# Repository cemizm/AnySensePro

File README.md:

# AnySense Pro
The AnySense Pro (aka 2.0) is an onboard flight logger and real-time telemetry system for (mainly) multicopters with versatile interfacing to various flight controllers, sensors and telemetry protocols. It is a further development of the [AnySense](https://github.com/cemizm/AnySense) and provides a more powerfull MCU (STM32F3) an SD-Card interface and USB connectivity for configuration and updates. A detailed description of the AnySense Pro can be found in the [manual](Dokumentation/AnySense_Pro_EN_.pdf) and in sources of the [main application](Firmware/shared/Application/source).

## Features
The aim of the AnySense Pro is to build a bridge between multiple proprietary systems and protocols in order to reduce the total take-off weight of the flight object. This is achived by reusing any existing sensor (source) of the integrated flight controller in a multicopter, and feeding the telemetry data to various sinks like the onboard SD-Card or real-time telemetrie return channel. 

### Flight Controller (source)
The AnySense Pro supports a wide range of open source and commercial flight controllers. A full list of provided sensors of each flight controller can be found in the [Manual](Dokumentation/AnySense_Pro_EN_.pdf). The flight controller connector provides 5V power supply, a CAN-Bus interface and full-duplex uart interface. 

| | |
|:---------:|:-----------:|
|  |  |

* [DJI Naza-M V1 / Lite](https://www.dji.com/de/naza-m-lite/feature)
* [DJI Naza-M V2](https://www.dji.com/de/naza-m-v2)
* [DJI Wookong](https://www.dji.com/de/wookong-m)
* [DJI A2](https://www.dji.com/de/a2)
* [DJI Phantom 2](https://www.dji.com/de/phantom-2)
* [3DR Pixhawk](https://docs.px4.io/master/en/flight_controller/mro_pixhawk.html)
* [Tarot ZYX-M](http://www.tarotrc.com/Product/Detail.aspx?Lang=en&Id=65341cc3-7941-4a12-84ea-8abc58bd59e7)
* [Align MRS](https://www.align.com.tw/index.php/download-en/mrs/)

Depending on the flight control, a corresponding cable with connectors and pin assignment is required. The pin assignment defines which hardware interface is used. The pinout of the flight controller connector on the AnySense Pro can be found in the [Schematics](Hardware/Pro/AnySensePro.pdf) or in some [example cables](Hardware/Kabel/CANBusKabel.pdf).

### FrSky Sensor (source)
Additionally to the integrated sensor of the flight controller, it is possible to use sensor of the vendor FrSky to obtain further telemetry data like a current sensor to measure total current consumption or a cell voltage sensor to monitor individual cells of the battery pack. The full list of supported sensors and implementation details can be found in the [source code](Firmware/shared/Application/source/SensorFrSky.cpp).

| | |
|:---------:|:-----------:|
|  |  |

The FrSky sensors run as a bus system and can therefore be daisy-chained together. for this purpose, each sensor offers two interconnected ports. The AnySense Pro acts as the master and each sensor operates as a slave. 

### USB
The USB interface of the AnySense Pro is used for configuration and firmware updates. The AnySense Pro implements an [USB-CDC device](Firmware/shared/Middleware/USB/source/USBCDCDevice.cpp) for serial communication with the host. The [host driver](Firmware/shared/driver/AnySensePro.inf) for the AnySense Pro uses [Microsoft provided in-box driver](https://docs.microsoft.com/en-us/windows-hardware/drivers/usbcon/usb-driver-installation-based-on-compatible-ids) with custom vendor and product ids. The AnySense Studio is a .NET WPF Application and can be used for configuration and firmware updates.
| | |
|:---------:|:-----------:|
|  |  |

### Micro SD (sink)

### Telemetry (sink)

### MAVLink OSD (sink)

## Project / Repository structure 

### Hardware
### Firmware
### GroundTools
### Dokumnetation

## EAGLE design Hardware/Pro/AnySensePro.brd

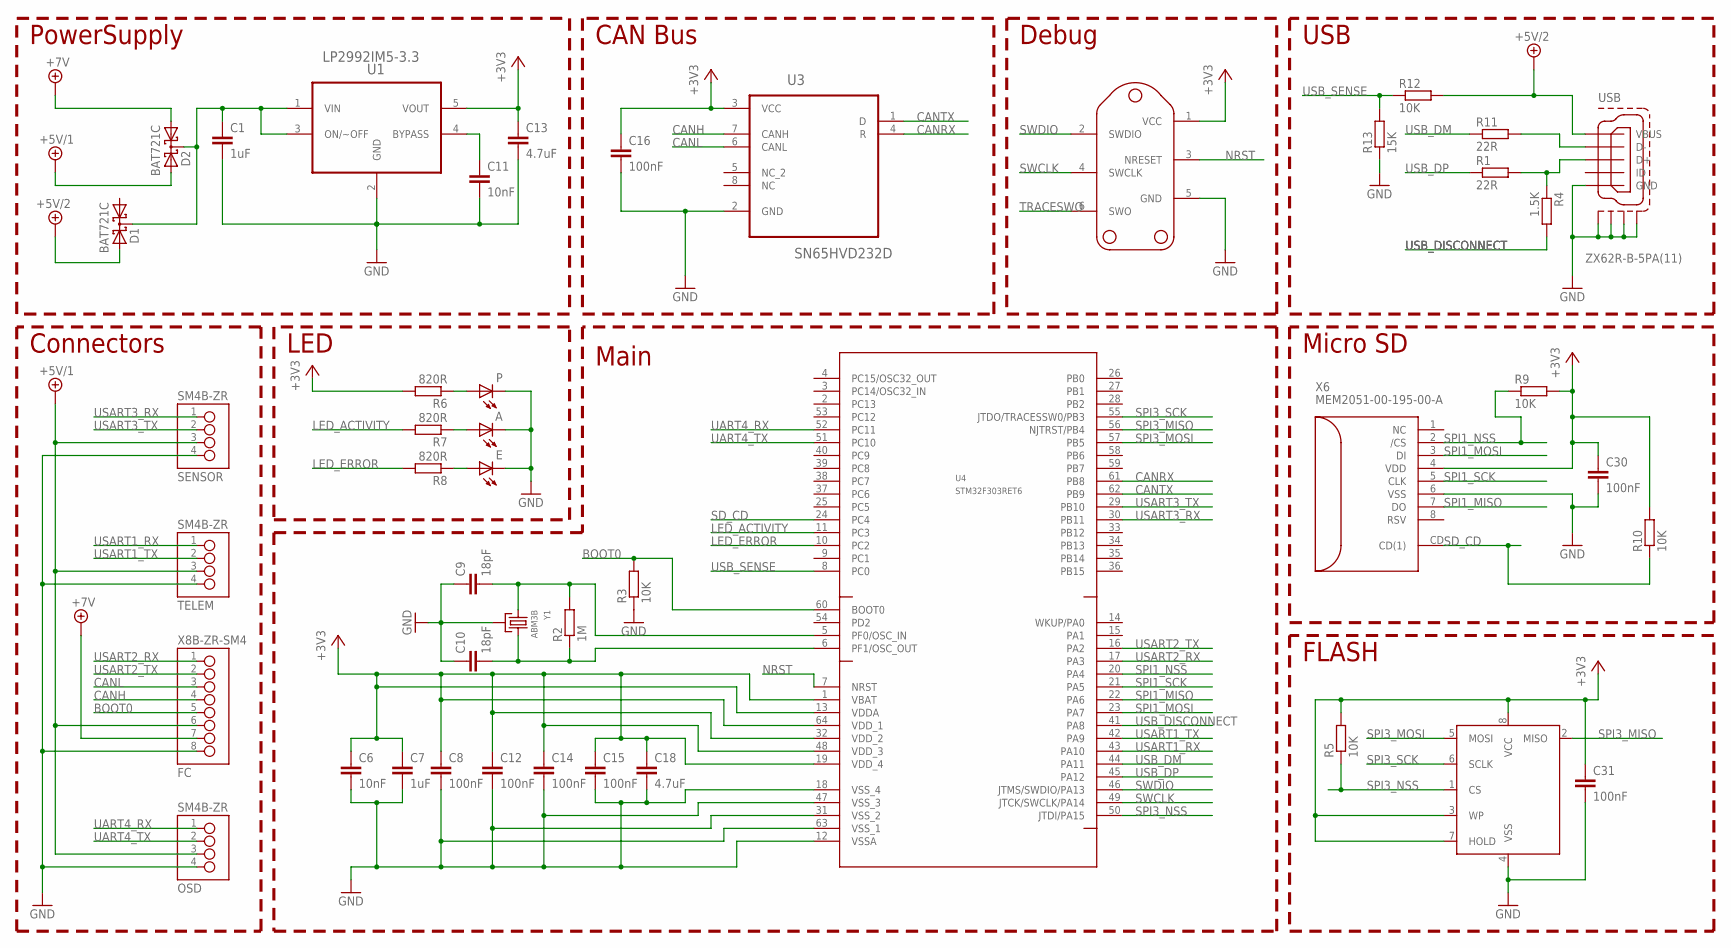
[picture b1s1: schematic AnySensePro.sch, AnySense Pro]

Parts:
A: LEDCHIP-LED0603; CHIP-LED0603
C1: 1uF; C0603K
C6, C11: 10nF; C0402K
C7: 1uF; C0402K
C8, C12, C14, C15, C16, C30, C31: 100nF; C0402K
C9, C10: 18pF; C0402K
C13, C18: 4.7uF; C0603K
D1, D2: BAT721C; SOT23
E: LEDCHIP-LED0603; CHIP-LED0603
FC: X8B-ZR-SM4; S8B-ZR-SM4
OSD: SM4B-ZR; S4B-ZR-SM4
P: LEDCHIP-LED0603; CHIP-LED0603
R1, R11: 22R; R0402
R2: 1M; R0402
R3, R5, R9, R10, R12: 10K; R0402
R4: 1.5K; R0402
R6, R7, R8: 820R; R0402
R13: 15K; R0402
SENSOR: SM4B-ZR; S4B-ZR-SM4
TELEM: SM4B-ZR; S4B-ZR-SM4
U1: LP2992IM5-3.3; SOT-23
U3: SN65HVD232D; SOIC127P600X175-8N
U4: STM32F303RET6; LQFP64
U6: M25P16VMN6P; M25P16
USB: ZX62R-B-5PA(11)
X6: MEM2051-00-195-00-A; MEM2051
X7: TC2030-IDC-NL; TC2030-IDC
Y1: ABM3B; 5X3.2MM

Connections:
+3V3: C6.1, C7.1, C8.1, C12.1, C13.1, C14.1, C15.1, C16.1, C18.1, C30.1, C31.1, R5.2, R6.2, R9.2, R10.2, U1.5 (VOUT), U3.3 (VCC), U4.1 (VBAT), U4.13 (VDDA), U4.19 (VDD_4), U4.32 (VDD_2), U4.48 (VDD_3), U4.64 (VDD_1), U6.3 (WP), U6.7 (HOLD), U6.8 (VCC), X6.4 (VDD), X7.1 (VCC)
+5V/1: D2.2 (A2), FC.6, OSD.3, SENSOR.3, TELEM.3
+5V/2: D1.2 (A2), R12.2, USB.1 (VBUS)
+7V: D2.1 (A1), FC.7
BOOT0: FC.5, R3.2, U4.60 (BOOT0)
CANH: FC.4, U3.7 (CANH)
CANL: FC.3, U3.6 (CANL)
CANRX: U3.4 (R), U4.61 (PB8)
CANTX: U3.1 (D), U4.62 (PB9)
GND: A.C, C1.2, C6.2, C7.2, C8.2, C9.1, C10.1, C11.2, C12.2, C13.2, C14.2, C15.2, C16.2, C18.2, C30.2, C31.2, E.C, FC.8, OSD.4, P.C, R3.1, R13.1, SENSOR.4, TELEM.4, U1.2 (GND), U3.2 (GND), U4.12 (VSSA), U4.18 (VSS_4), U4.31 (VSS_2), U4.47 (VSS_3), U4.63 (VSS_1), U6.4 (VSS), USB.5 (GND), USB.M1 (S1), USB.M2 (S2), USB.M3 (S3), USB.M4 (S4), X6.6 (VSS), X7.5 (GND), Y1.2 (GND), Y1.4 (GND)
LED_ACTIVITY: R7.2, U4.11 (PC3)
LED_ERROR: R8.2, U4.10 (PC2)
unnamed: C1.1, D1.3 (CC), D2.3 (CC), U1.1 (VIN), U1.3 (ON/~OFF)
unnamed: C10.2, R2.1, U4.6 (PF1/OSC_OUT), Y1.3 (2)
unnamed: C11.1, U1.4 (BYPASS)
unnamed: C9.2, R2.2, U4.5 (PF0/OSC_IN), Y1.1
unnamed: P.A, R6.1
unnamed: A.A, R7.1
unnamed: E.A, R8.1
NRST: U4.7 (NRST), X7.3 (NRESET)
SD_CD: R10.1, U4.24 (PC4), X6.CD (CD(1))
SPI1_MISO: U4.22 (PA6), X6.7 (DO)
SPI1_MOSI: U4.23 (PA7), X6.3 (DI)
SPI1_NSS: R9.1, U4.20 (PA4), X6.2 (/CS)
SPI1_SCK: U4.21 (PA5), X6.5 (CLK)
SPI3_MISO: U4.56 (NJTRST/PB4), U6.2 (MISO)
SPI3_MOSI: U4.57 (PB5), U6.5 (MOSI)
SPI3_NSS: R5.1, U4.50 (JTDI/PA15), U6.1 (CS)
SPI3_SCK: U4.55 (JTDO/TRACESSW0/PB3), U6.6 (SCLK)
SWCLK: U4.49 (JTCK/SWCLK/PA14), X7.4 (SWCLK)
SWDIO: U4.46 (JTMS/SWDIO/PA13), X7.2 (SWDIO)
TRACESWO: X7.6 (SWO)
UART4_RX: OSD.1, U4.52 (PC11)
UART4_TX: OSD.2, U4.51 (PC10)
USART1_RX: TELEM.1, U4.43 (PA10)
USART1_TX: TELEM.2, U4.42 (PA9)
USART2_RX: FC.1, U4.17 (PA3)
USART2_TX: FC.2, U4.16 (PA2)
USART3_RX: SENSOR.1, U4.30 (PB11)
USART3_TX: SENSOR.2, U4.29 (PB10)
USB_D+: R1.2, R4.1, USB.3 (D+)
USB_D-: R11.2, USB.2 (D-)
USB_DISCONNECT: R4.2, U4.41 (PA8)
USB_DM: R11.1, U4.44 (PA11)
USB_DP: R1.1, U4.45 (PA12)
USB_SENSE: R12.1, R13.2, U4.8 (PC0)

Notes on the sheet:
PowerSupply
Connectors
USB
Main
Micro SD
CAN Bus
LED
FLASH
Debug

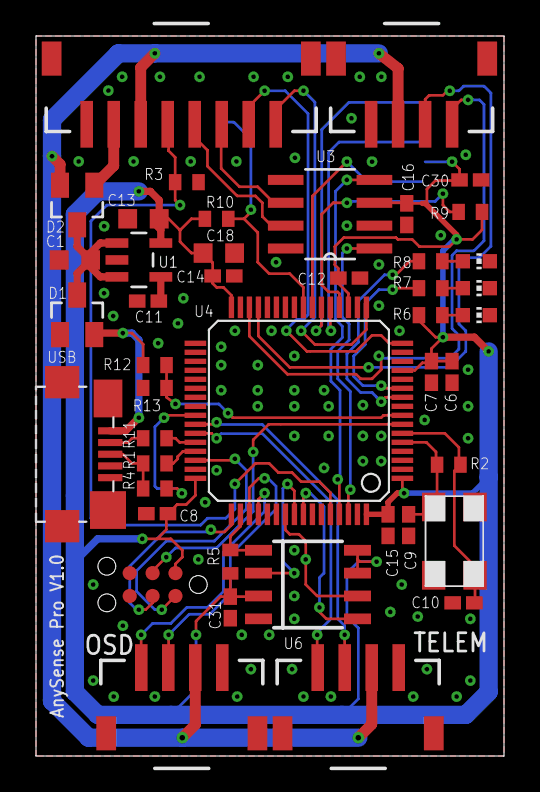
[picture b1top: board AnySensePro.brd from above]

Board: 2 copper layers, 26.0 x 40.0 mm, 45 parts (1 on the bottom side), 45 nets.

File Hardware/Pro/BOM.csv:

"Qty";"Value";"Device";"Package";"Parts";"Description";"MPN";"OC_FARNELL";"OC_NEWARK";"PACKAGE";"SUPPLIER";
"1";"";"LEDCHIP-LED0603";"CHIP-LED0603";"P";"LED";"";"2468791RL";"";"";"";
"1";"";"LEDCHIP-LED0603";"CHIP-LED0603";"E";"LED";"";"2468792RL";"";"";"";
"1";"";"LEDCHIP-LED0603";"CHIP-LED0603";"A";"LED";"";"2468793RL";"";"";"";
"1";"1.5K";"R-EU_R0402";"R0402";"R4";"RESISTOR, European symbol";"";"2302739RL";"";"";"";
"7";"100nF";"C-EUC0402K";"C0402K";"C8, C12, C14, C15, C16, C30, C31";"CAPACITOR, European symbol";"";"1759380RL";"";"";"";
"5";"10K";"R-EU_R0402";"R0402";"R3, R5, R9, R10, R12";"RESISTOR, European symbol";"";"2302739RL";"";"";"";
"2";"10nF";"C-EUC0402K";"C0402K";"C6, C11";"CAPACITOR, European symbol";"";"1758924RL";"";"";"";
"1";"15K";"R-EU_R0402";"R0402";"R13";"RESISTOR, European symbol";"";"2302739RL";"";"";"";
"2";"18pF";"C-EUC0402K";"C0402K";"C9, C10";"CAPACITOR, European symbol";"";"1758947RL";"";"";"";
"1";"1M";"R-EU_R0402";"R0402";"R2";"RESISTOR, European symbol";"";"2302957RL";"";"";"";
"1";"1uF";"C-EUC0402K";"C0402K";"C7";"CAPACITOR, European symbol";"";"2320776RL ";"";"";"";
"1";"1uF";"C-EUC0603K";"C0603K";"C1";"CAPACITOR, European symbol";"";"1759409RL";"";"";"";
"2";"22R";"R-EU_R0402";"R0402";"R1, R11";"RESISTOR, European symbol";"";"2302739RL";"";"";"";
"2";"4.7uF";"C-EUC0603K";"C0603K";"C13, C18";"CAPACITOR, European symbol";"";"2320818RL";"";"";"";
"3";"820";"R-EU_R0402";"R0402";"R6, R7, R8";"RESISTOR, European symbol";"";"2302628RL";"";"";"";
"1";"ABM3B";"ABM3B-8.000MHZ-B2-T";"5X3.2MM";"Y1";"";"";"2467818RL";"";"";"";
"2";"BAT721C";"BAT721C";"SOT23";"D1, D2";"Schottky Diodes";"";"1081199RL";"";"";"";
"1";"LP2992IM5-3.3";"LP2992IM5-3.3";"SOT-23";"U1";"Low-Dropout Regulator";"LP2992IM5-3.3";"1469141RL";"";"";"";
"1";"M25P16VMN6P";"M25P16VMN6P";"M25P16";"U6";"";"";"1734973";"";"";"";
"1";"MEM2051-00-195-00-A";"MEM2051-00-195-00-A";"MEM2051";"X6";"GLOBAL CONNECTOR TECHNOLOGY  MEM2051-00-195-00-A  STECKPLATZ, MICRO-SD, 8POS, SMTHersteller: GLOBAL CONNECTOR TECHNOLOGYBestellnummer: 2443092Herstellerteilenummer: MEM2051-00-195-00-A";"";"2443092";"";"";"";
"3";"SM4B-ZR";"SM4B-ZR";"S4B-ZR-SM4";"OSD, SENSOR, TELEM";"ZH Connector: 1.5mm pitch/Disconnectable Crimp style connector";"";"1830923";"";"";"";
"1";"SN65HVD232D";"SN65HVD232D";"SOIC127P600X175-8N";"U3";"3.3-V CAN TRANSCEIVERS";"SN65HVD232D";"1103107";"35K4890";"SOIC-8";"Texas Instruments";
"1";"STM32F303RET6";"STM32F303RET6";"LQFP64";"U4";"ARM® Cortex®-M4 32b MCU+FPU, up to 512KB Flash, 80KB SRAM, FMC, 4 ADCs, 2 DAC ch., 7 comp, 4 Op-Amp, 2.0-3.6 V";"";"2466939";"";"";"";
"1";"TC2030-IDC-NL";"TC2030-IDC-NL";"TC2030-IDC";"X7";"";"";"";"";"";"";
"1";"X8B-ZR-SM4";"X8B-ZR-SM4";"S8B-ZR-SM4";"FC";"JST ZH Connector";"";"1830925";"";"";"";
"1";"ZX62R-B-5PA(11)";"ZX62R-B-5PA(11)";"ZX62R-B-5PA(11)";"USB";"Micro USB Connector";"";"1645325";"";"";"";

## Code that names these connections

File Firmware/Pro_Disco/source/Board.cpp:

/*
 * Board.cpp
 *
 *  Created on: 11.09.2015
 *      Author: cem
 */

#include "Board.h"
#include <Interrupt.h>

#include <libopencm3/stm32/rcc.h>
#include <libopencm3/stm32/flash.h>
#include <libopencm3/stm32/can.h>
#include <libopencm3/stm32/st_usbfs.h>
#include <libopencm3/stm32/syscfg.h>

namespace Board
{

HAL::Pin LedActivity(GPIOE, RCC_GPIOE, GPIO10);
HAL::Pin LedError(GPIOE, RCC_GPIOE, GPIO11);

HAL::Pin USB_DP(GPIOA, RCC_GPIOA, GPIO11);
HAL::Pin USB_DM(GPIOA, RCC_GPIOA, GPIO12);
HAL::Pin USB_Disconnect(GPIOA, RCC_GPIOA, GPIO10);
HAL::Pin USB_Sense(GPIOA, RCC_GPIOA, GPIO9, EXTI19, NVIC_EXTI9_5_IRQ);

HAL::USB USB(RCC_USB, rcc_usb_prescale_1_5, USB_DP, USB_DM, GPIO_AF14, USB_Sense, USB_Disconnect, &st_usbfs_v2_usb_driver,
		NVIC_USB_LP_IRQ, NVIC_USB_HP_IRQ, NVIC_USB_WKUP_IRQ);

namespace FC
{

HAL::Pin CAN_RX(GPIOB, RCC_GPIOB, GPIO8);
HAL::Pin CAN_TX(GPIOB, RCC_GPIOB, GPIO9);

HAL::CAN CAN(CAN1, RCC_CAN, CAN_TX, CAN_RX, GPIO_AF9, NVIC_USB_HP_CAN1_TX_IRQ, NVIC_USB_LP_CAN1_RX0_IRQ, NVIC_CAN1_RX1_IRQ);

}

void SetupClock()
{
	/* Enable internal high-speed oscillator. */
	rcc_osc_on(HSI);
	rcc_wait_for_osc_ready(HSI);

	/* Select HSI as SYSCLK source. */
	rcc_set_sysclk_source(RCC_CFGR_SW_HSI);

	rcc_osc_bypass_enable(HSE);

	/* Enable external high-speed oscillator 8MHz. */
	rcc_osc_on(HSE);
	rcc_wait_for_osc_ready(HSE);

	rcc_set_hpre(RCC_CFGR_HPRE_DIV_NONE);
	rcc_set_ppre1(RCC_CFGR_PPRE1_DIV_2);
	rcc_set_ppre2(RCC_CFGR_PPRE2_DIV_NONE);

	rcc_set_main_pll_hsi(RCC_CFGR_PLLMUL_PLL_IN_CLK_X9);
	rcc_set_pll_source(RCC_CFGR_PLLSRC_HSE_PREDIV);

	/* Enable PLL oscillator and wait for it to stabilize. */
	rcc_osc_on(PLL);
	rcc_wait_for_osc_ready(PLL);

	/* Configure flash settings. */
	flash_set_ws(FLASH_ACR_PRFTBE | FLASH_ACR_LATENCY_2WS);

	/* Select PLL as SYSCLK source. */
	rcc_set_sysclk_source(RCC_CFGR_SW_PLL);

	/* Wait for PLL clock to be selected. */
	rcc_wait_for_sysclk_status(PLL);

	/* Set the peripheral clock frequencies used. */
	rcc_apb1_frequency = 36000000;
	rcc_apb2_frequency = 72000000;

	/* Disable internal high-speed oscillator. */
	rcc_osc_off(HSI);
}

void SystemInit()
{
	SetupClock();

	rcc_periph_clock_enable(rcc_periph_clken::RCC_SYSCFG);

	SYSCFG_MEMRM |= 1 << 5; //USB Remap

}

}

extern "C" void can1_rx1_isr()
{
	HAL::InterruptRegistry.HandleISR(NVIC_CAN1_RX1_IRQ);
}

extern "C" void usb_hp_can1_tx_isr()
{
	HAL::InterruptRegistry.HandleISR(NVIC_USB_HP_CAN1_TX_IRQ);
}

extern "C" void usb_lp_can1_rx0_isr()
{
	HAL::InterruptRegistry.HandleISR(NVIC_USB_LP_CAN1_RX0_IRQ);
}

extern "C" void usb_hp_isr()
{
	HAL::InterruptRegistry.HandleISR(NVIC_USB_HP_IRQ);
}

extern "C" void usb_lp_isr()
{
	HAL::InterruptRegistry.HandleISR(NVIC_USB_LP_IRQ);
}

extern "C" void usb_wkup_isr()
{
	HAL::InterruptRegistry.HandleISR(NVIC_USB_WKUP_IRQ);
}

extern "C" void exti9_5_isr()
{
	HAL::InterruptRegistry.HandleISR(NVIC_EXTI9_5_IRQ);
}

extern "C" void exti4_isr()
{
	HAL::InterruptRegistry.HandleISR(NVIC_EXTI4_IRQ);
}

extern "C" void dma1_channel2_isr()
{
	HAL::InterruptRegistry.HandleISR(NVIC_DMA1_CHANNEL2_IRQ);
}

extern "C" void dma1_channel3_isr()
{
	HAL::InterruptRegistry.HandleISR(NVIC_DMA1_CHANNEL3_IRQ);
}

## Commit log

2015-09-03 Initial Hardware commit
2015-09-03 Order Codes added
2015-09-04 Kalkulation, Datasheet
2015-09-09 Kalkulation, Dokumentation
2015-09-15 Initial Firmware commit
2015-09-19 Datasheets moved
2015-09-19 Datasheets added
2015-09-28 BLE Modul
2015-09-28 Hardware redesign
2015-09-28 added USB and CAN to HAL
2015-09-28 BlueNRG driver
2015-09-28 USB Driver and CDC, MSC support
2015-09-28 Queue and Pool utilities added
2015-09-28 Firmware Project updated
2015-09-28 Hardware Libraries added and Calculation updated
2015-09-28 Windows USB driver
2015-09-28 USB changes
2015-09-29 AnySense Pro Kabel Drawings
2015-09-29 AnySense Pro V1.1
2015-09-29 AnySense Pro Anfrage pcb-pool.com
2015-09-29 Basic FatFS Infrastructure added
2015-09-30 Eurocircuits Order
2015-10-02 SPI SDCard Library completed (stable)
2015-10-08 Namespace Utils corrected
2015-10-08 Farnell OC's updated and paste pad reduction removed.
2015-10-27 Final HW Design
2015-10-27 MAVLink Library added
2015-10-27 libopencm3 updated, usb reworked
2015-10-27 Storage Interface updated, SD Card Stable
2015-10-27 OSAL: Moved into own namespace
2015-10-27 Utils added
2015-10-27 lot changes
2015-10-27 USBWorker: Pool/Queue replaced with OSAL::Channel
2015-10-27 Small fixes on DJI Naza Telemetry
2016-02-13 Simplify USB CDC Device
2016-02-13 Changes...
2016-02-14 Initial communication AnySense Studio
2016-02-14 remove local files
2016-02-14 upgrade to libopencm3 version
2016-02-14 add ignores for Visual Studio
2016-02-14 documentation
2016-02-14 MavLink messages linked to VS solution
2016-02-25 Folding Interrupt Forwarding
2016-02-26 unused files
2016-02-26 Spiffs integrated
2016-02-26 disabled copying commons.xml in mavlink generating script
2016-02-26 Transfer Firmware to flash
2016-02-28 disable warnings
2016-02-29 Initial Bootloader commit
2016-02-29 Jump To Bootloader
2016-02-29 Async wait for m25p16 erase op
2016-02-29 project specific spiff configuration file
2016-02-29 boot loader remove delay on start (hold boot loader time as short as possible)
2016-03-01 VisibiltyConverter added
2016-03-01 Grouping of USB events reduced to get fast reconnect events
2016-03-01 Initial Auto Updater
2016-03-01 added base layer for Mavlink for future use
2016-03-01 removed format of flash drive while mounting
2016-03-01 Bootloader Memory shrinked
2016-03-01 Driver installation Package, Bootstrapper and prerequisite
2016-03-02 Dialog Controller for ViewModels
2016-03-02 Bindable Bing Map control
2016-03-02 Remove grouping of device change events for faster reconnect
2016-03-02 Automatic firmware update on connect
2016-03-02 Version update
2016-03-03 MAVLink Flight Controller added
2016-03-03 UI Stuff
2016-03-03 MAVLink Layer abstraction
2016-03-04 DJI A2 first commit
2016-03-04 Roll Converter to invert roll view
2016-03-04 Sensor Store Set cells
2016-03-04 Telemetry analysing
2016-03-04 start device polling async
2016-03-05 Debug logging
2016-03-05 Cleanup main
2016-03-05 SPI Flash Autorelease file and read file
2016-03-05 Load, Save Configuration
2016-03-05 AnySense Studio: Debug log printing
2016-03-05 Filter polling serial devices
2016-03-05 force firmware update shortcut
2016-03-05 garbage collection on flash drive
2016-03-05 System Service
2016-03-05 Heartbeat & log dji receive timeout
2016-03-06 Sensor Store: save available Sensors
2016-03-06 System Service calculate values, house keeping
2016-03-06 reorganize usb initialization and singleton handling
2016-03-06 increase threads and re-prioritize workers
2016-03-06 Thread Memory space corrected
2016-03-06 Flash Storage initialization reorganized
2016-03-06 Configuration Changed Handler
2016-03-06 Telemetry Controller initial commit
2016-03-06 Split USB transmission in endpoint packet size chunks before transmission
2016-03-06 Configuration Protocol and UI
2016-03-06 Notify configuration changed
2016-03-06 Empty data templates for all protocol settings
2016-03-07 BugFix: usb device name retrieval
2016-03-07 configuration structure corrected
2016-03-07 TelemetryAdapter Interface changed, Mavlink telemetry finished
2016-03-08 Protocol dependent settings
2016-03-08 Get specific cell from store
2016-03-08 Configuration versioning
2016-03-08 extended usart functions
2016-03-08 Telemetry FrSky done.
2016-03-08 MAVLink Battery pack extended
2016-03-08 libopencm3 ref
2016-03-08 wix lib path corrected
2016-03-08 Application revision update
2016-03-08 Template class for handling telemetry enum to class type
2016-03-09 BugFix flight time
2016-03-09 signaling in interrupt modified
2016-03-09 new usart features
2016-03-09 telemetry HoTT finished (unstable)
2016-03-09 BugFix config validation key
2016-03-09 AnySense Studio scroll viewer in Settings
2016-03-09 Telemetry Hott typo corrected
2016-03-09 Multiplex
2016-03-11 Telemetry Adapter Base class restructured
2016-03-11 remove unused headers
2016-03-11 blink codes changed
2016-03-11 Multiplex: new telemetry values
2016-03-11 AnySense Studio appearance
2016-03-12 AnySense Studio final style
2016-03-12 CAN error timeout
2016-03-12 Firmware: SensorController created, initial commit frsky sensor
2016-03-12 AnySense Studio show sw version
2016-03-14 FrSky lipo data structure added
2016-03-14 FrSky Sensor polling finished
2016-03-14 MAVLink channel for various communications
2016-03-15 MAVLink Flightmode mapping changed
2016-03-15 MAVLinkComm send message routine simplified, methods and members modifier changed to protected for inheritance
2016-03-15 FC USART corrected
2016-03-17 Pixhawk added
2016-03-17 AnySense Studio shadow effect on map
2016-03-17 Logging Controller Skeleton
2016-03-17 HAL: Timer added
2016-03-17 Timer for Telemetry Port
2016-03-17 Logging Controller in process added
2016-03-17 Basic Jeti implementations
2016-03-17 stack size calculation
2016-03-17 flash size reduced duo boot loader space
2016-03-17 Prioritize Interrupts
2016-03-17 fattime
2016-03-18 AnySense Studio, Driver and installer signing
2016-03-19 usart receive timeout typo corrected
2016-03-19 Futaba Telemetry finished
2016-03-20 AnySense Studio Futaba configuration
2016-03-20 AnySense Studio configuration validation
2016-03-20 AnySense Studio Jeti Configuration
2016-03-20 AnySense Studio Mavlink configuration serialization/deserialization
2016-03-20 AnySense Studio HoTT configuration BugFix validation key
2016-03-20 AnySense Studio Spektrum configuration
2016-03-20 Release Script and embedded resource path for firmware binary
2016-03-21 Flash-Tool
2016-03-21 AnySense Studio BugFix exception on send message
2016-03-22 GPS Signal Quality check
2016-03-22 Bug on configuration changed
2016-03-22 Jeti Telemetry finished
2016-03-22 BugFix Futaba Telemetry configuration
2016-03-22 Jeti finished
2016-03-22 Remove MAVLink in/out buffers
2016-03-22 Telemetry Jeti sign fix
2016-03-22 Telemetry Jeti consumption decimal point corrected
2016-03-22 SystemService consumption calculator factor corrected
2016-03-22 Pixhawk fixed datetime
2016-03-22 Flight session and permanent flight number counter
2016-03-22 DateTime Util class added and SensorStore::GPSTime replaced
2016-03-22 Pixhawk DateTime
2016-03-22 Logging finished
2016-03-22 AnySense Studio BugFix: IOException while disposing a disconnected serial connection
2016-03-22 process no return
2016-03-22 Release Logging finished
2016-03-23 Memory optimizations
2016-03-23 configuration struct reserved bytes changed to union
2016-03-23 DateTime.cpp moved to source folder
2016-03-25 SensorData.Capacity changed to 32bit
2016-03-25 Endianess and BCD conversion utils
2016-03-25 HAL i2c
2016-03-25 leave HSI enabled for i2c usage
2016-03-25 passing i2c interface to telemetry controller
2016-03-25 AnySense Studio: possibly fixing unhandled exception
2016-03-26 Telemetry Spektrum finished
2016-03-26 AnySense Pro Version 2.0.1
2016-03-31 BugFix: Jeti Telemetry descriptions was transferred, even if the channel was disabled
2016-04-06 flasher script delay before new flash
2016-04-06 reorganize folder structure
2016-04-19 FC Alive refactored
2016-04-19 Tarot support
2016-04-19 Voltage, Distance Alarm
2016-04-19 Online Update
2016-06-01 Jeti RPM Sensor added
2016-06-22 FC Align Initial commit
2016-07-03 Move into include folder
2016-07-04 APS-M Align Support
2016-07-07 Tarot v1.50 support
2016-07-11 untrack eagle.epf
2016-07-11 BugFix Naza Home Position
2016-07-15 Gehäuse initial version
2016-07-19 Gehäuse first print
2016-07-22 Gehäuse V2
2016-07-27 Gehäuse V3
2016-08-01 Gehäuse V4
2016-08-04 Gehäuse V5: Schnapper verstärkt
2016-09-01 BugFix: FrSky Telemetry Fix Type cirrected
2016-11-29 Get Time since boot
2016-11-29 AnySense Verpackung
2016-11-29 DJI save velocity
2016-11-29 GPS Home Position measurement
2016-11-29 extended logging + flir vue pro msgs
2016-11-29 delay logging
2016-11-29 BugFix DateTime
2016-11-29 Release 2.2.3
2022-04-23 rename umlaute
2022-04-24 add license and some readme
2022-04-24 more readme
